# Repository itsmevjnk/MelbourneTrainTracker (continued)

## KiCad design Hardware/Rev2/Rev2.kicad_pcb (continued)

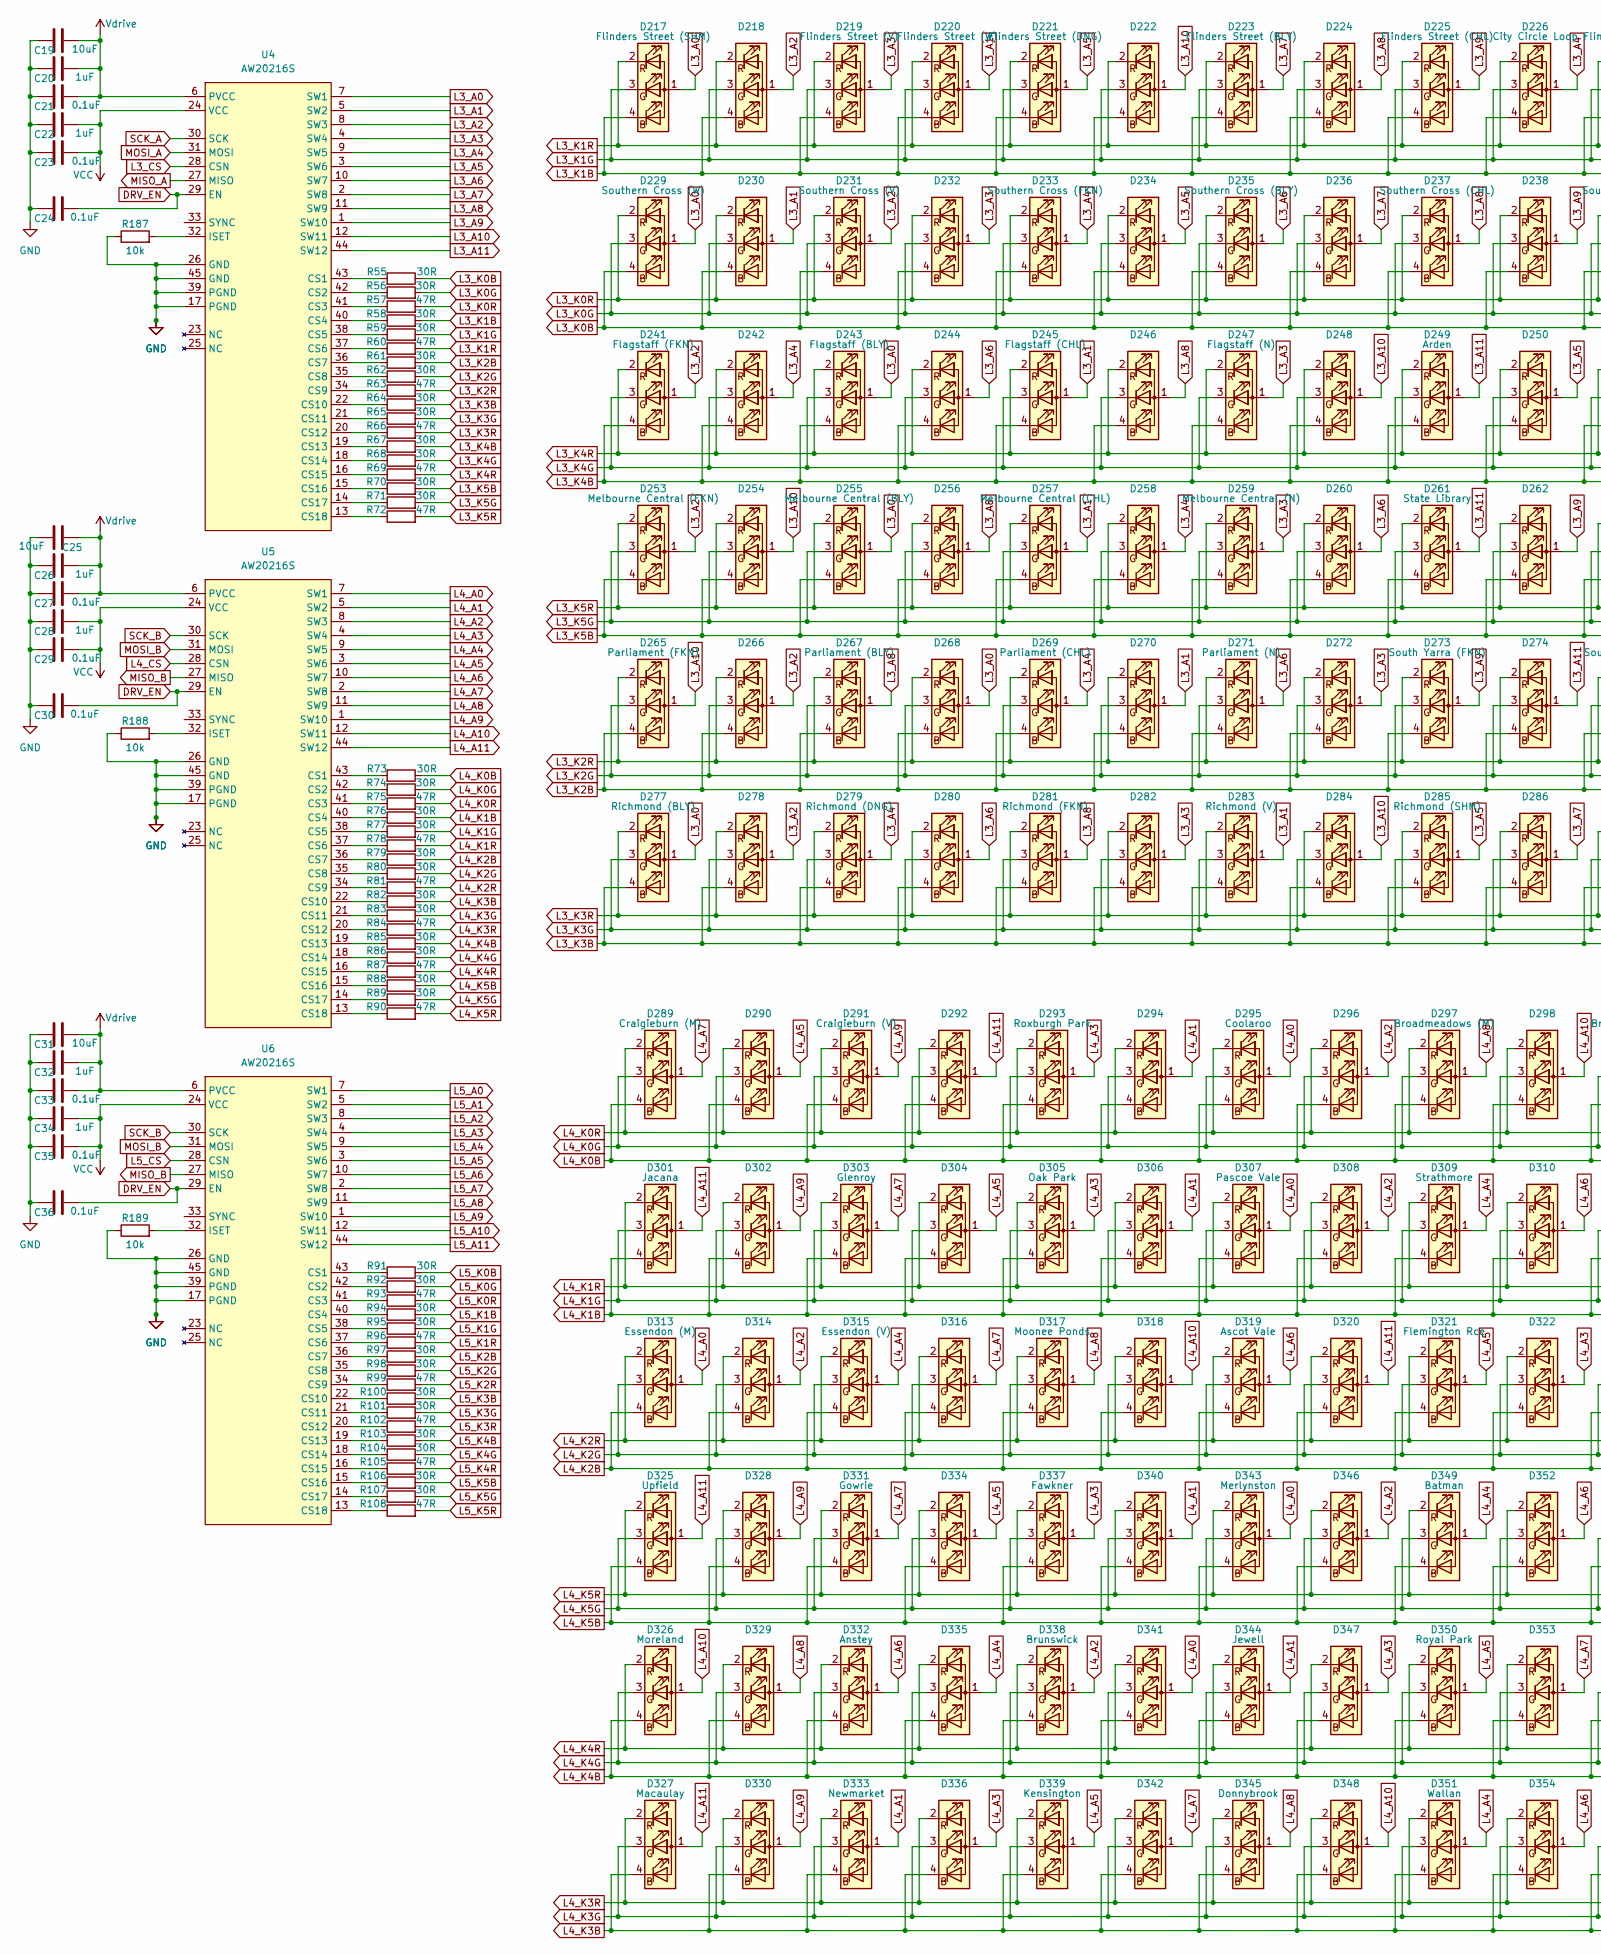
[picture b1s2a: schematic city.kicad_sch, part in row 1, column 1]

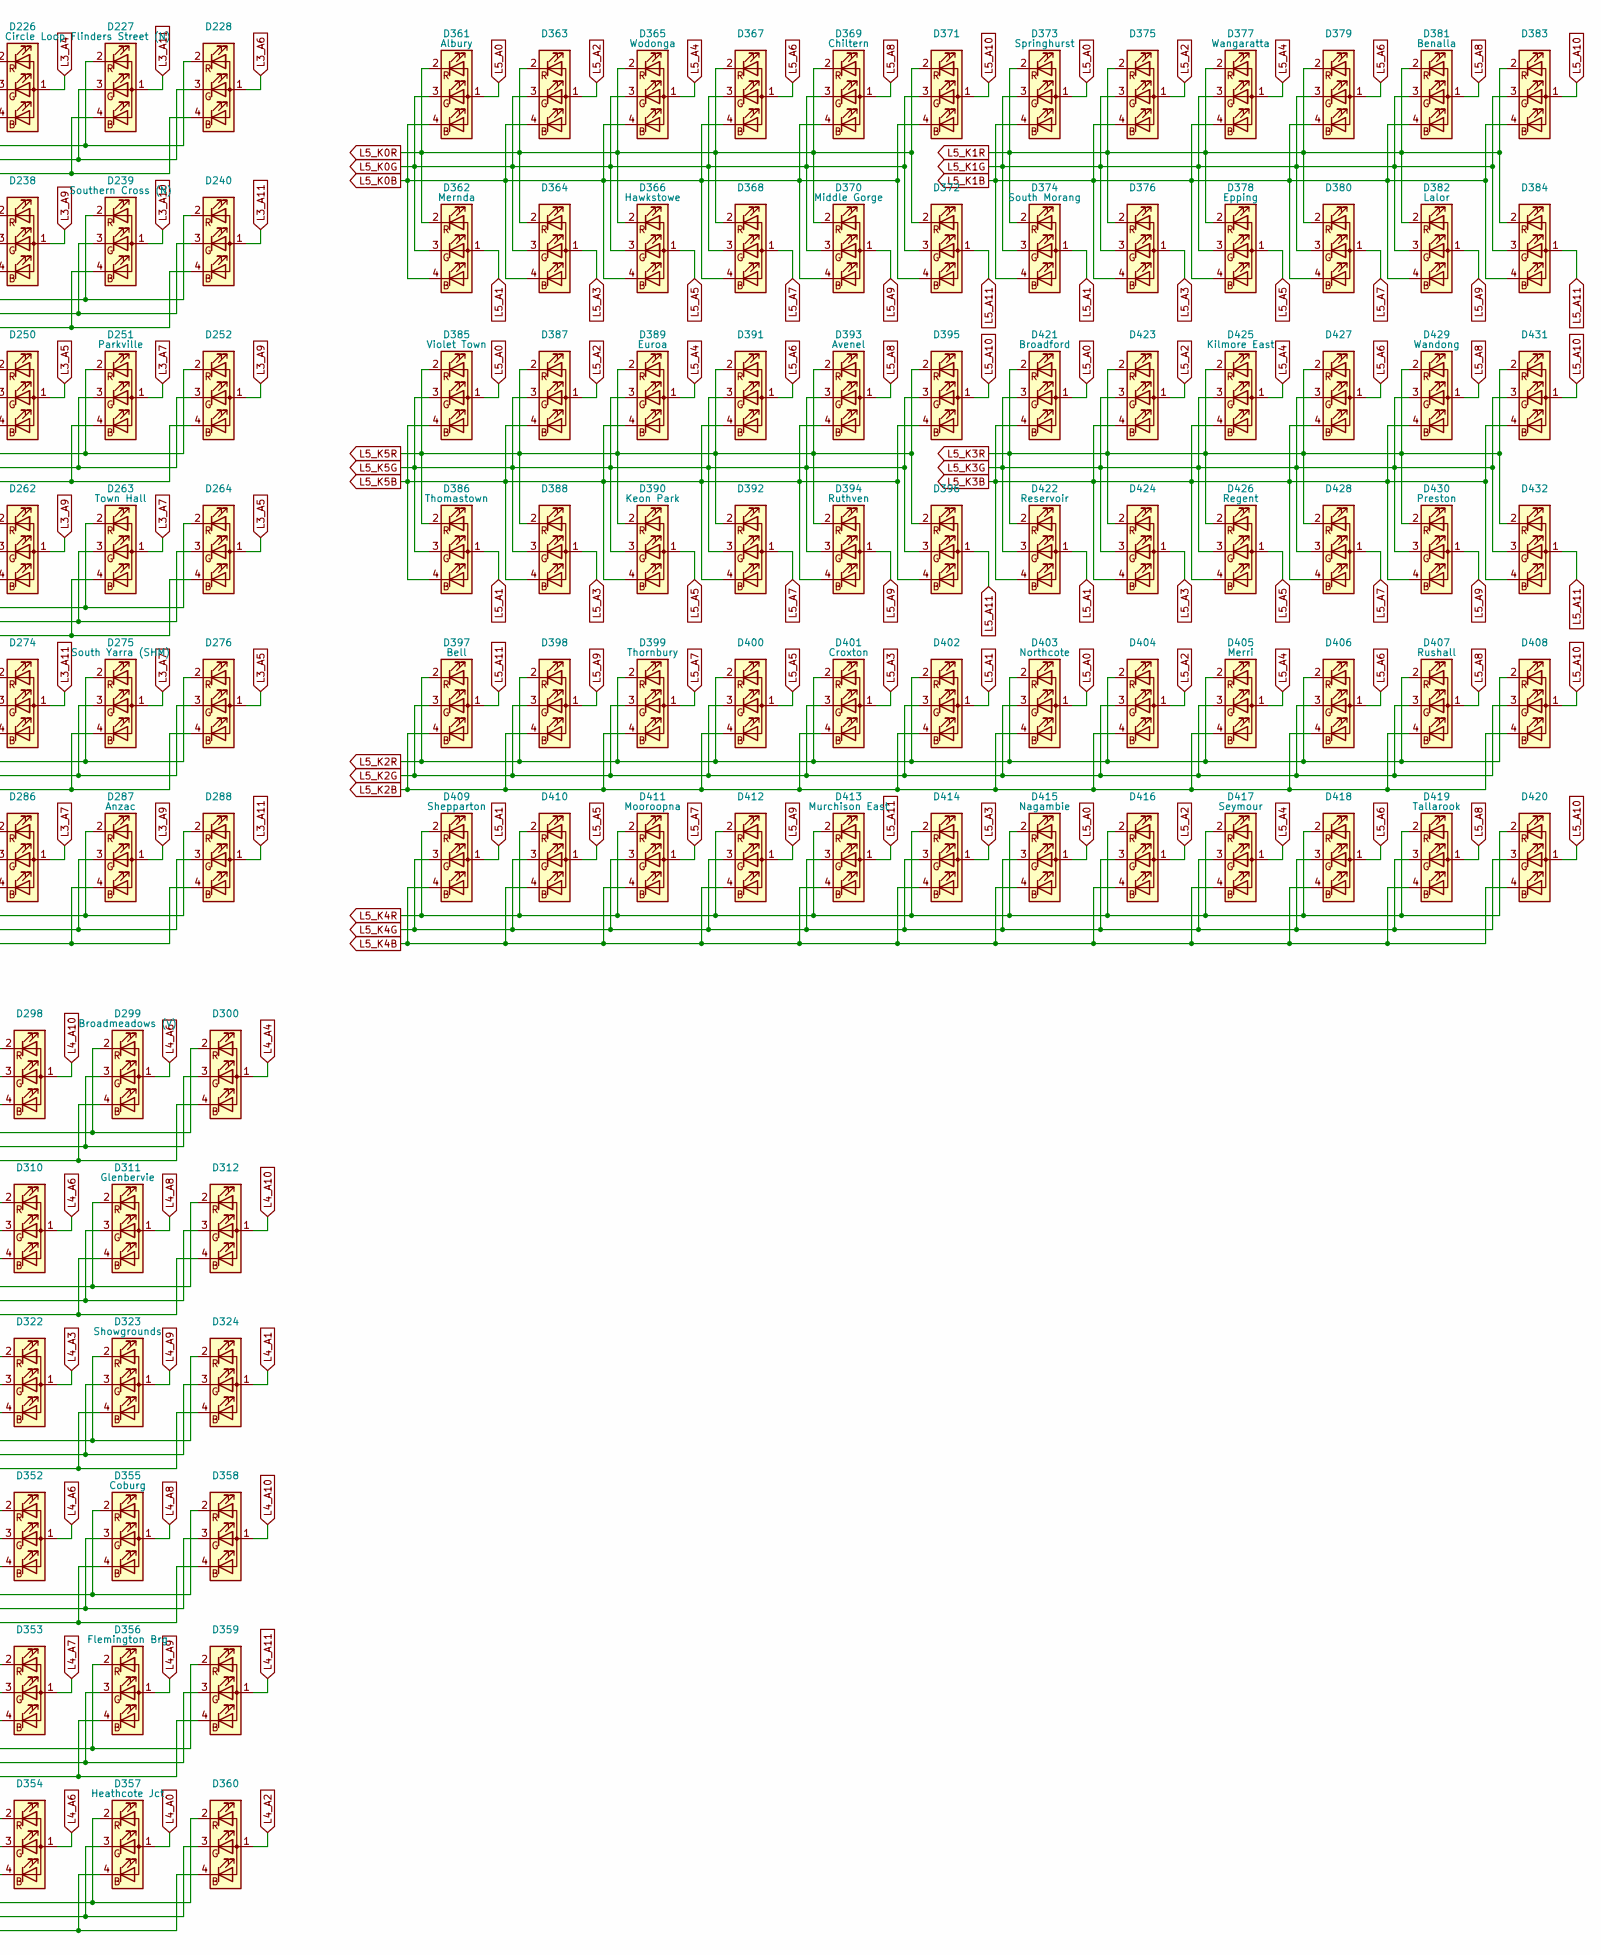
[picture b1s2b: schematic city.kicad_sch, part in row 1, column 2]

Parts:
C19, C25, C31: 10uF; C_0805_2012Metric_Pad1.18x1.45mm_HandSolder; MPN C380332
C20, C22, C26, C28, C32, C34: 1uF; C_0603_1608Metric_Pad1.08x0.95mm_HandSolder; MPN C6119849
C21, C23, C24, C27, C29, C30, C33, C35, C36: 0.1uF; C_0603_1608Metric_Pad1.08x0.95mm_HandSolder; MPN C14663
D217, D218, D219, D220, D221, D222, D223, D224, D225, D226, D227, D228, D229, D230, D231, D232, D233, D234, D235, D236, D237, D238, D239, D240, D241, D242, D243, D244, D245, D246, D247, D248, D249, D250, D251, D252, D253, D254, D255, D256, D257, D258, D259, D260, D261, D262, D263, D264, D265, D266, D267, D268, D269, D270, D271, D272, D273, D274, D275, D276, D277, D278, D279, D280, D281, D282, D283, D284, D285, D286, D287, D288, D289, D290, D291, D292, D293, D294, D295, D296, D297, D298, D299, D300, D301, D302, D303, D304, D305, D306, D307, D308, D309, D310, D311, D312, D313, D314, D315, D316, D317, D318, D319, D320, D321, D322, D323, D324, D325, D326, D327, D328, D329, D330, D331, D332, D333, D334, D335, D336, D337, D338, D339, D340, D341, D342, D343, D344, D345, D346, D347, D348, D349, D350, D351, D352, D353, D354, D355, D356, D357, D358, D359, D360, D361, D362, D363, D364, D365, D366, D367, D368, D369, D370, D371, D372, D373, D374, D375, D376, D377, D378, D379, D380, D381, D382, D383, D384, D385, D386, D387, D388, D389, D390, D391, D392, D393, D394, D395, D396, D397, D398, D399, D400, D401, D402, D403, D404, D405, D406, D407, D408, D409, D410, D411, D412, D413, D414, D415, D416, D417, D418, D419, D420, D421, D422, D423, D424, D425, D426, D427, D428, D429, D430, D431, D432: XL-B1010RGBT-HF; LED_RGB_Xinglight-1010; MPN C22464515
R55, R56, R58, R59, R61, R62, R64, R65, R67, R68, R70, R71, R73, R74, R76, R77, R79, R80, R82, R83, R85, R86, R88, R89, R91, R92, R94, R95, R97, R98, R100, R101, R103, R104, R106, R107: 30R; R_0805_2012Metric_Pad1.20x1.40mm_HandSolder
R57, R60, R63, R66, R69, R72, R75, R78, R81, R84, R87, R90, R93, R96, R99, R102, R105, R108: 47R; R_0805_2012Metric_Pad1.20x1.40mm_HandSolder
R187, R188, R189: 10k; R_0603_1608Metric_Pad0.98x0.95mm_HandSolder; MPN C2930231
U4, U5, U6: AW20216S; QFN-44-1EP_5x5mm_P0.4mm_EP2.45x2.45mm; MPN C7385556

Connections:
+3.3V: C22.2, C23.2, C28.2, C29.2, C34.2, C35.2, U4.24 (VCC), U5.24 (VCC), U6.24 (VCC); also elsewhere on the board
+5V: C19.2, C20.2, C21.2, C25.1, C26.2, C27.2, C31.2, C32.2, C33.2, U4.6 (PVCC), U5.6 (PVCC), U6.6 (PVCC); also elsewhere on the board
DRV_EN: C24.2, C30.2, C36.2, U4.29 (EN), U5.29 (EN), U6.29 (EN); also elsewhere on the board
GND: C19.1, C20.1, C21.1, C22.1, C23.1, C24.1, C25.2, C26.1, C27.1, C28.1, C29.1, C30.1, C31.1, C32.1, C33.1, C34.1, C35.1, C36.1, R187.1, R188.1, R189.1, U4.17 (PGND), U4.26 (GND), U4.39 (PGND), U4.45 (GND), U5.17 (PGND), U5.26 (GND), U5.39 (PGND), U5.45 (GND), U6.17 (PGND), U6.26 (GND), U6.39 (PGND), U6.45 (GND); also elsewhere on the board
L3_A0: D217.1 (A), D229.1 (A), D243.1 (A), D255.1 (A), D268.1 (A), D277.1 (A), U4.7 (SW1)
L3_A1: D220.1 (A), D230.1 (A), D245.1 (A), D257.1 (A), D270.1 (A), D283.1 (A), U4.5 (SW2)
L3_A2: D218.1 (A), D231.1 (A), D241.1 (A), D253.1 (A), D266.1 (A), D278.1 (A), U4.8 (SW3)
L3_A3: D219.1 (A), D232.1 (A), D247.1 (A), D259.1 (A), D272.1 (A), D282.1 (A), U4.4 (SW4)
L3_A4: D226.1 (A), D233.1 (A), D242.1 (A), D258.1 (A), D269.1 (A), D279.1 (A), U4.9 (SW5)
L3_A5: D221.1 (A), D234.1 (A), D250.1 (A), D264.1 (A), D276.1 (A), D285.1 (A), U4.3 (SW6)
L3_A6: D228.1 (A), D235.1 (A), D244.1 (A), D260.1 (A), D271.1 (A), D280.1 (A), U4.10 (SW7)
L3_A7: D223.1 (A), D236.1 (A), D251.1 (A), D263.1 (A), D275.1 (A), D286.1 (A), U4.2 (SW8)
L3_A8: D224.1 (A), D237.1 (A), D246.1 (A), D256.1 (A), D267.1 (A), D281.1 (A), U4.11 (SW9)
L3_A9: D225.1 (A), D238.1 (A), D252.1 (A), D262.1 (A), D273.1 (A), D287.1 (A), U4.1 (SW10)
L3_A10: D222.1 (A), D239.1 (A), D248.1 (A), D254.1 (A), D265.1 (A), D284.1 (A), U4.12 (SW11)
L3_A11: D227.1 (A), D240.1 (A), D249.1 (A), D261.1 (A), D274.1 (A), D288.1 (A), U4.44 (SW12)
L3_CS: U4.28 (CSN); also elsewhere on the board
L3_K0B: D229.4 (BK), D230.4 (BK), D231.4 (BK), D232.4 (BK), D233.4 (BK), D234.4 (BK), D235.4 (BK), D236.4 (BK), D237.4 (BK), D238.4 (BK), D239.4 (BK), D240.4 (BK), R55.1
L3_K0G: D229.3 (GK), D230.3 (GK), D231.3 (GK), D232.3 (GK), D233.3 (GK), D234.3 (GK), D235.3 (GK), D236.3 (GK), D237.3 (GK), D238.3 (GK), D239.3 (GK), D240.3 (GK), R56.2
L3_K0R: D229.2 (RK), D230.2 (RK), D231.2 (RK), D232.2 (RK), D233.2 (RK), D234.2 (RK), D235.2 (RK), D236.2 (RK), D237.2 (RK), D238.2 (RK), D239.2 (RK), D240.2 (RK), R57.2
L3_K1B: D217.4 (BK), D218.4 (BK), D219.4 (BK), D220.4 (BK), D221.4 (BK), D222.4 (BK), D223.4 (BK), D224.4 (BK), D225.4 (BK), D226.4 (BK), D227.4 (BK), D228.4 (BK), R58.2
L3_K1G: D217.3 (GK), D218.3 (GK), D219.3 (GK), D220.3 (GK), D221.3 (GK), D222.3 (GK), D223.3 (GK), D224.3 (GK), D225.3 (GK), D226.3 (GK), D227.3 (GK), D228.3 (GK), R59.2
L3_K1R: D217.2 (RK), D218.2 (RK), D219.2 (RK), D220.2 (RK), D221.2 (RK), D222.2 (RK), D223.2 (RK), D224.2 (RK), D225.2 (RK), D226.2 (RK), D227.2 (RK), D228.2 (RK), R60.2
L3_K2B: D265.4 (BK), D266.4 (BK), D267.4 (BK), D268.4 (BK), D269.4 (BK), D270.4 (BK), D271.4 (BK), D272.4 (BK), D273.4 (BK), D274.4 (BK), D275.4 (BK), D276.4 (BK), R61.2
L3_K2G: D265.3 (GK), D266.3 (GK), D267.3 (GK), D268.3 (GK), D269.3 (GK), D270.3 (GK), D271.3 (GK), D272.3 (GK), D273.3 (GK), D274.3 (GK), D275.3 (GK), D276.3 (GK), R62.2
L3_K2R: D265.2 (RK), D266.2 (RK), D267.2 (RK), D268.2 (RK), D269.2 (RK), D270.2 (RK), D271.2 (RK), D272.2 (RK), D273.2 (RK), D274.2 (RK), D275.2 (RK), D276.2 (RK), R63.2
L3_K3B: D277.4 (BK), D278.4 (BK), D279.4 (BK), D280.4 (BK), D281.4 (BK), D282.4 (BK), D283.4 (BK), D284.4 (BK), D285.4 (BK), D286.4 (BK), D287.4 (BK), D288.4 (BK), R64.2
L3_K3G: D277.3 (GK), D278.3 (GK), D279.3 (GK), D280.3 (GK), D281.3 (GK), D282.3 (GK), D283.3 (GK), D284.3 (GK), D285.3 (GK), D286.3 (GK), D287.3 (GK), D288.3 (GK), R65.2
L3_K3R: D277.2 (RK), D278.2 (RK), D279.2 (RK), D280.2 (RK), D281.2 (RK), D282.2 (RK), D283.2 (RK), D284.2 (RK), D285.2 (RK), D286.2 (RK), D287.2 (RK), D288.2 (RK), R66.2
L3_K4B: D241.4 (BK), D242.4 (BK), D243.4 (BK), D244.4 (BK), D245.4 (BK), D246.4 (BK), D247.4 (BK), D248.4 (BK), D249.4 (BK), D250.4 (BK), D251.4 (BK), D252.4 (BK), R67.2
L3_K4G: D241.3 (GK), D242.3 (GK), D243.3 (GK), D244.3 (GK), D245.3 (GK), D246.3 (GK), D247.3 (GK), D248.3 (GK), D249.3 (GK), D250.3 (GK), D251.3 (GK), D252.3 (GK), R68.2
L3_K4R: D241.2 (RK), D242.2 (RK), D243.2 (RK), D244.2 (RK), D245.2 (RK), D246.2 (RK), D247.2 (RK), D248.2 (RK), D249.2 (RK), D250.2 (RK), D251.2 (RK), D252.2 (RK), R69.2
L3_K5B: D253.4 (BK), D254.4 (BK), D255.4 (BK), D256.4 (BK), D257.4 (BK), D258.4 (BK), D259.4 (BK), D260.4 (BK), D261.4 (BK), D262.4 (BK), D263.4 (BK), D264.4 (BK), R70.2
L3_K5G: D253.3 (GK), D254.3 (GK), D255.3 (GK), D256.3 (GK), D257.3 (GK), D258.3 (GK), D259.3 (GK), D260.3 (GK), D261.3 (GK), D262.3 (GK), D263.3 (GK), D264.3 (GK), R71.2
L3_K5R: D253.2 (RK), D254.2 (RK), D255.2 (RK), D256.2 (RK), D257.2 (RK), D258.2 (RK), D259.2 (RK), D260.2 (RK), D261.2 (RK), D262.2 (RK), D263.2 (RK), D264.2 (RK), R72.2
L4_A0: D295.1 (A), D307.1 (A), D313.1 (A), D341.1 (A), D343.1 (A), D357.1 (A), U5.7 (SW1)
L4_A1: D294.1 (A), D306.1 (A), D324.1 (A), D333.1 (A), D340.1 (A), D344.1 (A), U5.5 (SW2)
L4_A2: D296.1 (A), D308.1 (A), D314.1 (A), D338.1 (A), D346.1 (A), D360.1 (A), U5.8 (SW3)
L4_A3: D293.1 (A), D305.1 (A), D322.1 (A), D336.1 (A), D337.1 (A), D347.1 (A), U5.4 (SW4)
L4_A4: D300.1 (A), D309.1 (A), D315.1 (A), D335.1 (A), D349.1 (A), D351.1 (A), U5.9 (SW5)
L4_A5: D290.1 (A), D304.1 (A), D321.1 (A), D334.1 (A), D339.1 (A), D350.1 (A), U5.3 (SW6)
L4_A6: D299.1 (A), D310.1 (A), D319.1 (A), D332.1 (A), D352.1 (A), D354.1 (A), U5.10 (SW7)
L4_A7: D289.1 (A), D303.1 (A), D316.1 (A), D331.1 (A), D342.1 (A), D353.1 (A), U5.2 (SW8)
L4_A8: D297.1 (A), D311.1 (A), D317.1 (A), D329.1 (A), D345.1 (A), D355.1 (A), U5.11 (SW9)
L4_A9: D291.1 (A), D302.1 (A), D323.1 (A), D328.1 (A), D330.1 (A), D356.1 (A), U5.1 (SW10)
L4_A10: D298.1 (A), D312.1 (A), D318.1 (A), D326.1 (A), D348.1 (A), D358.1 (A), U5.12 (SW11)
L4_A11: D292.1 (A), D301.1 (A), D320.1 (A), D325.1 (A), D327.1 (A), D359.1 (A), U5.44 (SW12)
L4_CS: U5.28 (CSN); also elsewhere on the board
L4_K0B: D289.4 (BK), D290.4 (BK), D291.4 (BK), D292.4 (BK), D293.4 (BK), D294.4 (BK), D295.4 (BK), D296.4 (BK), D297.4 (BK), D298.4 (BK), D299.4 (BK), D300.4 (BK), R73.1
L4_K0G: D289.3 (GK), D290.3 (GK), D291.3 (GK), D292.3 (GK), D293.3 (GK), D294.3 (GK), D295.3 (GK), D296.3 (GK), D297.3 (GK), D298.3 (GK), D299.3 (GK), D300.3 (GK), R74.2
L4_K0R: D289.2 (RK), D290.2 (RK), D291.2 (RK), D292.2 (RK), D293.2 (RK), D294.2 (RK), D295.2 (RK), D296.2 (RK), D297.2 (RK), D298.2 (RK), D299.2 (RK), D300.2 (RK), R75.2
L4_K1B: D301.4 (BK), D302.4 (BK), D303.4 (BK), D304.4 (BK), D305.4 (BK), D306.4 (BK), D307.4 (BK), D308.4 (BK), D309.4 (BK), D310.4 (BK), D311.4 (BK), D312.4 (BK), R76.2
L4_K1G: D301.3 (GK), D302.3 (GK), D303.3 (GK), D304.3 (GK), D305.3 (GK), D306.3 (GK), D307.3 (GK), D308.3 (GK), D309.3 (GK), D310.3 (GK), D311.3 (GK), D312.3 (GK), R77.2
L4_K1R: D301.2 (RK), D302.2 (RK), D303.2 (RK), D304.2 (RK), D305.2 (RK), D306.2 (RK), D307.2 (RK), D308.2 (RK), D309.2 (RK), D310.2 (RK), D311.2 (RK), D312.2 (RK), R78.2
L4_K2B: D313.4 (BK), D314.4 (BK), D315.4 (BK), D316.4 (BK), D317.4 (BK), D318.4 (BK), D319.4 (BK), D320.4 (BK), D321.4 (BK), D322.4 (BK), D323.4 (BK), D324.4 (BK), R79.2
L4_K2G: D313.3 (GK), D314.3 (GK), D315.3 (GK), D316.3 (GK), D317.3 (GK), D318.3 (GK), D319.3 (GK), D320.3 (GK), D321.3 (GK), D322.3 (GK), D323.3 (GK), D324.3 (GK), R80.2
L4_K2R: D313.2 (RK), D314.2 (RK), D315.2 (RK), D316.2 (RK), D317.2 (RK), D318.2 (RK), D319.2 (RK), D320.2 (RK), D321.2 (RK), D322.2 (RK), D323.2 (RK), D324.2 (RK), R81.2
L4_K3B: D327.4 (BK), D330.4 (BK), D333.4 (BK), D336.4 (BK), D339.4 (BK), D342.4 (BK), D345.4 (BK), D348.4 (BK), D351.4 (BK), D354.4 (BK), D357.4 (BK), D360.4 (BK), R82.2
L4_K3G: D327.3 (GK), D330.3 (GK), D333.3 (GK), D336.3 (GK), D339.3 (GK), D342.3 (GK), D345.3 (GK), D348.3 (GK), D351.3 (GK), D354.3 (GK), D357.3 (GK), D360.3 (GK), R83.2
L4_K3R: D327.2 (RK), D330.2 (RK), D333.2 (RK), D336.2 (RK), D339.2 (RK), D342.2 (RK), D345.2 (RK), D348.2 (RK), D351.2 (RK), D354.2 (RK), D357.2 (RK), D360.2 (RK), R84.2
L4_K4B: D326.4 (BK), D329.4 (BK), D332.4 (BK), D335.4 (BK), D338.4 (BK), D341.4 (BK), D344.4 (BK), D347.4 (BK), D350.4 (BK), D353.4 (BK), D356.4 (BK), D359.4 (BK), R85.2
L4_K4G: D326.3 (GK), D329.3 (GK), D332.3 (GK), D335.3 (GK), D338.3 (GK), D341.3 (GK), D344.3 (GK), D347.3 (GK), D350.3 (GK), D353.3 (GK), D356.3 (GK), D359.3 (GK), R86.2
L4_K4R: D326.2 (RK), D329.2 (RK), D332.2 (RK), D335.2 (RK), D338.2 (RK), D341.2 (RK), D344.2 (RK), D347.2 (RK), D350.2 (RK), D353.2 (RK), D356.2 (RK), D359.2 (RK), R87.2
L4_K5B: D325.4 (BK), D328.4 (BK), D331.4 (BK), D334.4 (BK), D337.4 (BK), D340.4 (BK), D343.4 (BK), D346.4 (BK), D349.4 (BK), D352.4 (BK), D355.4 (BK), D358.4 (BK), R88.2
L4_K5G: D325.3 (GK), D328.3 (GK), D331.3 (GK), D334.3 (GK), D337.3 (GK), D340.3 (GK), D343.3 (GK), D346.3 (GK), D349.3 (GK), D352.3 (GK), D355.3 (GK), D358.3 (GK), R89.2
L4_K5R: D325.2 (RK), D328.2 (RK), D331.2 (RK), D334.2 (RK), D337.2 (RK), D340.2 (RK), D343.2 (RK), D346.2 (RK), D349.2 (RK), D352.2 (RK), D355.2 (RK), D358.2 (RK), R90.2
L5_A0: D361.1 (A), D373.1 (A), D385.1 (A), D403.1 (A), D415.1 (A), D421.1 (A), U6.7 (SW1)
L5_A1: D362.1 (A), D374.1 (A), D386.1 (A), D402.1 (A), D409.1 (A), D422.1 (A), U6.5 (SW2)
L5_A2: D363.1 (A), D375.1 (A), D387.1 (A), D404.1 (A), D416.1 (A), D423.1 (A), U6.8 (SW3)
L5_A3: D364.1 (A), D376.1 (A), D388.1 (A), D401.1 (A), D414.1 (A), D424.1 (A), U6.4 (SW4)
L5_A4: D365.1 (A), D377.1 (A), D389.1 (A), D405.1 (A), D417.1 (A), D425.1 (A), U6.9 (SW5)
L5_A5: D366.1 (A), D378.1 (A), D390.1 (A), D400.1 (A), D410.1 (A), D426.1 (A), U6.3 (SW6)
L5_A6: D367.1 (A), D379.1 (A), D391.1 (A), D406.1 (A), D418.1 (A), D427.1 (A), U6.10 (SW7)
L5_A7: D368.1 (A), D380.1 (A), D392.1 (A), D399.1 (A), D411.1 (A), D428.1 (A), U6.2 (SW8)
L5_A8: D369.1 (A), D381.1 (A), D393.1 (A), D407.1 (A), D419.1 (A), D429.1 (A), U6.11 (SW9)
L5_A9: D370.1 (A), D382.1 (A), D394.1 (A), D398.1 (A), D412.1 (A), D430.1 (A), U6.1 (SW10)
L5_A10: D371.1 (A), D383.1 (A), D395.1 (A), D408.1 (A), D420.1 (A), D431.1 (A), U6.12 (SW11)
L5_A11: D372.1 (A), D384.1 (A), D396.1 (A), D397.1 (A), D413.1 (A), D432.1 (A), U6.44 (SW12)
L5_CS: U6.28 (CSN); also elsewhere on the board
L5_K0B: D361.4 (BK), D362.4 (BK), D363.4 (BK), D364.4 (BK), D365.4 (BK), D366.4 (BK), D367.4 (BK), D368.4 (BK), D369.4 (BK), D370.4 (BK), D371.4 (BK), D372.4 (BK), R91.1
L5_K0G: D361.3 (GK), D362.3 (GK), D363.3 (GK), D364.3 (GK), D365.3 (GK), D366.3 (GK), D367.3 (GK), D368.3 (GK), D369.3 (GK), D370.3 (GK), D371.3 (GK), D372.3 (GK), R92.2
L5_K0R: D361.2 (RK), D362.2 (RK), D363.2 (RK), D364.2 (RK), D365.2 (RK), D366.2 (RK), D367.2 (RK), D368.2 (RK), D369.2 (RK), D370.2 (RK), D371.2 (RK), D372.2 (RK), R93.2
L5_K1B: D373.4 (BK), D374.4 (BK), D375.4 (BK), D376.4 (BK), D377.4 (BK), D378.4 (BK), D379.4 (BK), D380.4 (BK), D381.4 (BK), D382.4 (BK), D383.4 (BK), D384.4 (BK), R94.2
L5_K1G: D373.3 (GK), D374.3 (GK), D375.3 (GK), D376.3 (GK), D377.3 (GK), D378.3 (GK), D379.3 (GK), D380.3 (GK), D381.3 (GK), D382.3 (GK), D383.3 (GK), D384.3 (GK), R95.2
L5_K1R: D373.2 (RK), D374.2 (RK), D375.2 (RK), D376.2 (RK), D377.2 (RK), D378.2 (RK), D379.2 (RK), D380.2 (RK), D381.2 (RK), D382.2 (RK), D383.2 (RK), D384.2 (RK), R96.2
L5_K2B: D397.4 (BK), D398.4 (BK), D399.4 (BK), D400.4 (BK), D401.4 (BK), D402.4 (BK), D403.4 (BK), D404.4 (BK), D405.4 (BK), D406.4 (BK), D407.4 (BK), D408.4 (BK), R97.2
L5_K2G: D397.3 (GK), D398.3 (GK), D399.3 (GK), D400.3 (GK), D401.3 (GK), D402.3 (GK), D403.3 (GK), D404.3 (GK), D405.3 (GK), D406.3 (GK), D407.3 (GK), D408.3 (GK), R98.2
L5_K2R: D397.2 (RK), D398.2 (RK), D399.2 (RK), D400.2 (RK), D401.2 (RK), D402.2 (RK), D403.2 (RK), D404.2 (RK), D405.2 (RK), D406.2 (RK), D407.2 (RK), D408.2 (RK), R99.2
L5_K3B: D421.4 (BK), D422.4 (BK), D423.4 (BK), D424.4 (BK), D425.4 (BK), D426.4 (BK), D427.4 (BK), D428.4 (BK), D429.4 (BK), D430.4 (BK), D431.4 (BK), D432.4 (BK), R100.2
L5_K3G: D421.3 (GK), D422.3 (GK), D423.3 (GK), D424.3 (GK), D425.3 (GK), D426.3 (GK), D427.3 (GK), D428.3 (GK), D429.3 (GK), D430.3 (GK), D431.3 (GK), D432.3 (GK), R101.2
L5_K3R: D421.2 (RK), D422.2 (RK), D423.2 (RK), D424.2 (RK), D425.2 (RK), D426.2 (RK), D427.2 (RK), D428.2 (RK), D429.2 (RK), D430.2 (RK), D431.2 (RK), D432.2 (RK), R102.2
L5_K4B: D409.4 (BK), D410.4 (BK), D411.4 (BK), D412.4 (BK), D413.4 (BK), D414.4 (BK), D415.4 (BK), D416.4 (BK), D417.4 (BK), D418.4 (BK), D419.4 (BK), D420.4 (BK), R103.2
L5_K4G: D409.3 (GK), D410.3 (GK), D411.3 (GK), D412.3 (GK), D413.3 (GK), D414.3 (GK), D415.3 (GK), D416.3 (GK), D417.3 (GK), D418.3 (GK), D419.3 (GK), D420.3 (GK), R104.2
L5_K4R: D409.2 (RK), D410.2 (RK), D411.2 (RK), D412.2 (RK), D413.2 (RK), D414.2 (RK), D415.2 (RK), D416.2 (RK), D417.2 (RK), D418.2 (RK), D419.2 (RK), D420.2 (RK), R105.2
L5_K5B: D385.4 (BK), D386.4 (BK), D387.4 (BK), D388.4 (BK), D389.4 (BK), D390.4 (BK), D391.4 (BK), D392.4 (BK), D393.4 (BK), D394.4 (BK), D395.4 (BK), D396.4 (BK), R106.2
L5_K5G: D385.3 (GK), D386.3 (GK), D387.3 (GK), D388.3 (GK), D389.3 (GK), D390.3 (GK), D391.3 (GK), D392.3 (GK), D393.3 (GK), D394.3 (GK), D395.3 (GK), D396.3 (GK), R107.2
L5_K5R: D385.2 (RK), D386.2 (RK), D387.2 (RK), D388.2 (RK), D389.2 (RK), D390.2 (RK), D391.2 (RK), D392.2 (RK), D393.2 (RK), D394.2 (RK), D395.2 (RK), D396.2 (RK), R108.2
MISO_A: U4.27 (MISO); also elsewhere on the board
MISO_B: U5.27 (MISO), U6.27 (MISO); also elsewhere on the board
MOSI_A: U4.31 (MOSI); also elsewhere on the board
MOSI_B: U5.31 (MOSI), U6.31 (MOSI); also elsewhere on the board
unnamed: R55.2, U4.43 (CS1)
unnamed: R56.1, U4.42 (CS2)
unnamed: R57.1, U4.41 (CS3)
unnamed: R58.1, U4.40 (CS4)
unnamed: R59.1, U4.38 (CS5)
unnamed: R60.1, U4.37 (CS6)
unnamed: R61.1, U4.36 (CS7)
unnamed: R62.1, U4.35 (CS8)
unnamed: R63.1, U4.34 (CS9)
unnamed: R64.1, U4.22 (CS10)
unnamed: R65.1, U4.21 (CS11)
unnamed: R66.1, U4.20 (CS12)
unnamed: R67.1, U4.19 (CS13)
unnamed: R68.1, U4.18 (CS14)
unnamed: R69.1, U4.16 (CS15)
unnamed: R70.1, U4.15 (CS16)
unnamed: R71.1, U4.14 (CS17)
unnamed: R72.1, U4.13 (CS18)
unnamed: R187.2, U4.32 (ISET)
unnamed: R73.2, U5.43 (CS1)
unnamed: R74.1, U5.42 (CS2)
unnamed: R75.1, U5.41 (CS3)
unnamed: R76.1, U5.40 (CS4)
unnamed: R77.1, U5.38 (CS5)
unnamed: R78.1, U5.37 (CS6)
unnamed: R79.1, U5.36 (CS7)
unnamed: R80.1, U5.35 (CS8)
unnamed: R81.1, U5.34 (CS9)
unnamed: R82.1, U5.22 (CS10)
unnamed: R83.1, U5.21 (CS11)
unnamed: R84.1, U5.20 (CS12)
unnamed: R85.1, U5.19 (CS13)
unnamed: R86.1, U5.18 (CS14)
unnamed: R87.1, U5.16 (CS15)
unnamed: R88.1, U5.15 (CS16)
unnamed: R89.1, U5.14 (CS17)
unnamed: R90.1, U5.13 (CS18)
unnamed: R188.2, U5.32 (ISET)
unnamed: R91.2, U6.43 (CS1)
unnamed: R92.1, U6.42 (CS2)
unnamed: R93.1, U6.41 (CS3)
unnamed: R94.1, U6.40 (CS4)
unnamed: R95.1, U6.38 (CS5)
unnamed: R96.1, U6.37 (CS6)
unnamed: R97.1, U6.36 (CS7)
unnamed: R98.1, U6.35 (CS8)
unnamed: R99.1, U6.34 (CS9)
unnamed: R100.1, U6.22 (CS10)
unnamed: R101.1, U6.21 (CS11)
unnamed: R102.1, U6.20 (CS12)
unnamed: R103.1, U6.19 (CS13)
unnamed: R104.1, U6.18 (CS14)
unnamed: R105.1, U6.16 (CS15)
unnamed: R106.1, U6.15 (CS16)
unnamed: R107.1, U6.14 (CS17)
unnamed: R108.1, U6.13 (CS18)
unnamed: R189.2, U6.32 (ISET)
SCK_A: U4.30 (SCK); also elsewhere on the board
SCK_B: U5.30 (SCK), U6.30 (SCK); also elsewhere on the board

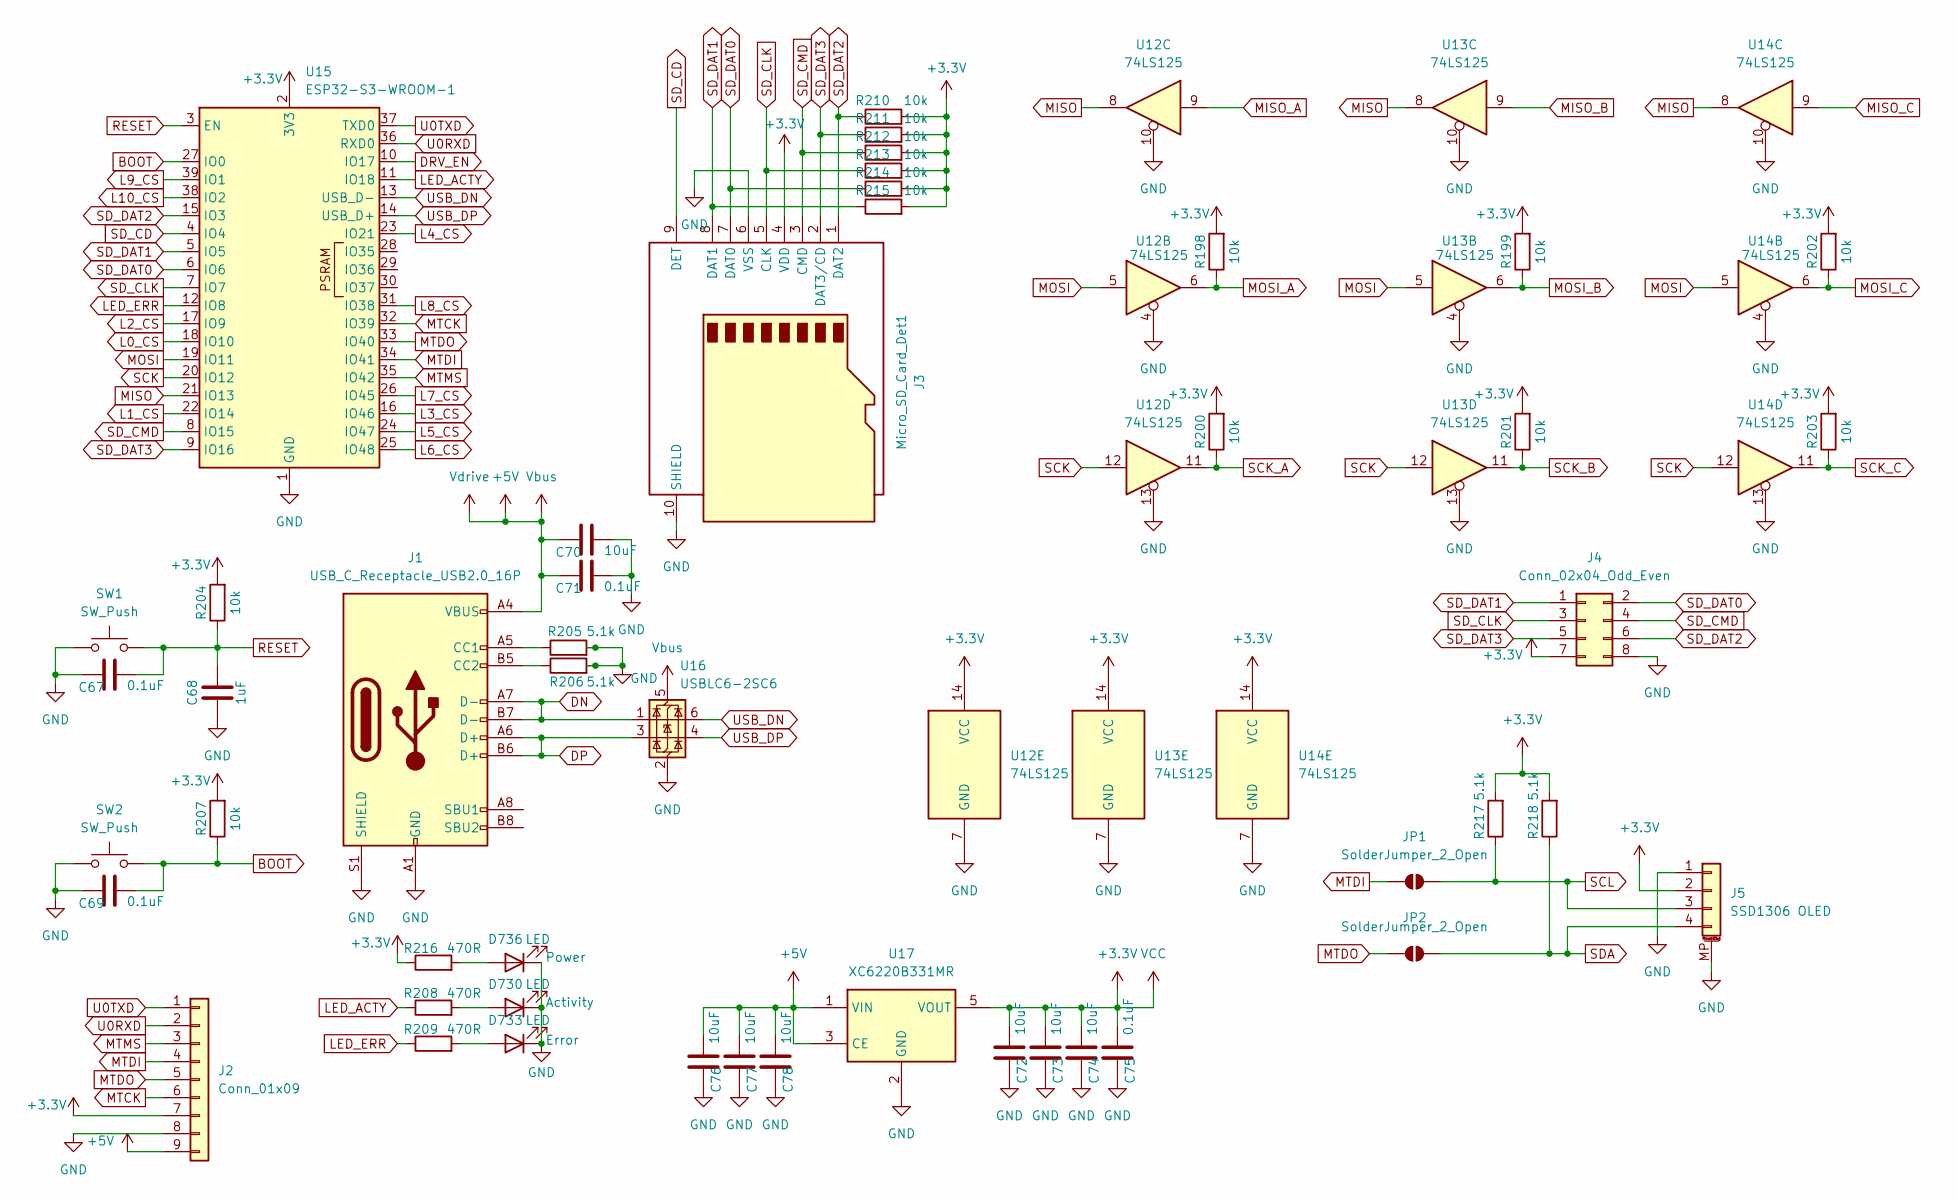
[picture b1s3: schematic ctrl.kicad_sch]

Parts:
C67, C69, C71, C75: 0.1uF; C_0603_1608Metric_Pad1.08x0.95mm_HandSolder; MPN C14663
C68: 1uF; C_0603_1608Metric_Pad1.08x0.95mm_HandSolder; MPN C6119849
C70, C72, C73, C74, C76, C77, C78: 10uF; C_0805_2012Metric_Pad1.18x1.45mm_HandSolder; MPN C380332
D730, D733, D736: LED; LED_1206_3216Metric_Pad1.42x1.75mm_HandSolder; MPN C965822
J1: USB_C_Receptacle_USB2.0_16P; ShouHan-USBC-16P-2MD; MPN C2765186
J2: Conn_01x09; PinHeader_1x09_P2.54mm_Vertical; MPN C49451372
J3: Micro_SD_Card_Det1; TFW11-N1S1-2000-A; MPN C22357898
J4: Conn_02x04_Odd_Even; PinHeader_2x04_P2.54mm_Vertical
J5: SSD1306 OLED; HS96L03W2C03
JP1, JP2: SolderJumper_2_Open; SolderJumper-2_P1.3mm_Open_TrianglePad1.0x1.5mm
R198, R199, R200, R201, R202, R203, R204, R207, R210, R211, R212, R213, R214, R215: 10k; R_0603_1608Metric_Pad0.98x0.95mm_HandSolder; MPN C15401
R205, R206, R217, R218: 5.1k; R_0603_1608Metric_Pad0.98x0.95mm_HandSolder; MPN C328370
R208, R209: 470R; R_0603_1608Metric_Pad0.98x0.95mm_HandSolder; MPN C23179
R216: 470R; R_0603_1608Metric_Pad0.98x0.95mm_HandSolder; MPN C2907127
SW1, SW2: SW_Push; SW_Push_1P1T_NO_E-Switch_TL3301NxxxxxG; MPN C5342967
U12, U13, U14: 74LS125; SO-14_3.9x8.65mm_P1.27mm; MPN C5138994
U15: ESP32-S3-WROOM-1; MPN C2913201
U16: USBLC6-2SC6; SOT-23-6
U17: XC6220B331MR; SOT-23-5

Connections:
+3.3V: C72.2, C73.2, C74.2, C75.2, J2.7, J3.4 (VDD), J4.7, J5.2, R198.2, R199.2, R200.2, R201.2, R202.2, R203.2, R204.2, R207.2, R210.2, R211.2, R212.2, R213.2, R214.2, R215.2, R216.1, R217.2, R218.2, U12.14 (VCC), U13.14 (VCC), U14.14 (VCC), U15.2 (3V3), U17.5 (VOUT); also elsewhere on the board
+5V: C70.1, C71.1, C76.2, C77.2, C78.2, J1.A4 (VBUS), J1.A9 (VBUS), J1.B4 (VBUS), J1.B9 (VBUS), J2.9, U16.5 (VBUS), U17.1 (VIN), U17.3 (CE); also elsewhere on the board
BOOT: C69.2, R207.1, SW2.2, U15.27 (IO0)
DN: J1.A7 (D-), J1.B7 (D-), U16.1 (I/O1)
DP: J1.A6 (D+), J1.B6 (D+), U16.3 (I/O2)
DRV_EN: U15.10 (IO17); also elsewhere on the board
GND: C67.1, C68.1, C69.1, C70.2, C71.2, C72.1, C73.1, C74.1, C75.1, C76.1, C77.1, C78.1, D730.1 (K), D733.1 (K), D736.1 (K), J1.A1 (GND), J1.A12 (GND), J1.B1 (GND), J1.B12 (GND), J1.S1 (SHIELD), J2.8, J3.6 (VSS), J3.10 (SHIELD), J4.8, J5.1, J5.MP (MountPin), R205.2, R206.2, SW1.1, SW2.1, U12.4, U12.7 (GND), U12.10, U12.13, U13.4, U13.7 (GND), U13.10, U13.13, U14.4, U14.7 (GND), U14.10, U14.13, U15.1 (GND), U15.40 (GND), U15.41 (GND), U16.2 (GND), U17.2 (GND); also elsewhere on the board
L0_CS: U15.18 (IO10); also elsewhere on the board
L1_CS: U15.22 (IO14); also elsewhere on the board
L2_CS: U15.17 (IO9); also elsewhere on the board
L3_CS: U15.16 (IO46); also elsewhere on the board
L4_CS: U15.23 (IO21); also elsewhere on the board
L5_CS: U15.24 (IO47); also elsewhere on the board
L6_CS: U15.25 (IO48); also elsewhere on the board
L7_CS: U15.26 (IO45); also elsewhere on the board
L8_CS: U15.31 (IO38); also elsewhere on the board
L9_CS: U15.39 (IO1); also elsewhere on the board
L10_CS: U15.38 (IO2); also elsewhere on the board
LED_ACTY: R208.1, U15.11 (IO18)
LED_ERR: R209.1, U15.12 (IO8)
MISO: U12.8, U13.8, U14.8, U15.21 (IO13)
MISO_A: U12.9; also elsewhere on the board
MISO_B: U13.9; also elsewhere on the board
MISO_C: U14.9; also elsewhere on the board
MOSI: U12.5, U13.5, U14.5, U15.19 (IO11)
MOSI_A: R198.1, U12.6; also elsewhere on the board
MOSI_B: R199.1, U13.6; also elsewhere on the board
MOSI_C: R202.1, U14.6; also elsewhere on the board
MTCK: J2.6, U15.32 (IO39)
MTDI: J2.4, JP1.1 (A), U15.34 (IO41)
MTDO: J2.5, JP2.1 (A), U15.33 (IO40)
MTMS: J2.3, U15.35 (IO42)
unnamed: D730.2 (A), R208.2
unnamed: D733.2 (A), R209.2
unnamed: D736.2 (A), R216.2
unnamed: J1.A5 (CC1), R205.1
unnamed: J1.B5 (CC2), R206.1
RESET: C67.2, C68.2, R204.1, SW1.2, U15.3 (EN)
SCK: U12.12, U13.12, U14.12, U15.20 (IO12)
SCK_A: R200.1, U12.11; also elsewhere on the board
SCK_B: R201.1, U13.11; also elsewhere on the board
SCK_C: R203.1, U14.11; also elsewhere on the board
SCL: J5.3, JP1.2 (B), R217.1
SDA: J5.4, JP2.2 (B), R218.1
SD_CD: J3.9 (DET), U15.4 (IO4)
SD_CLK: J3.5 (CLK), J4.3, R213.1, U15.7 (IO7)
SD_CMD: J3.3 (CMD), J4.4, R212.1, U15.8 (IO15)
SD_DAT0: J3.7 (DAT0), J4.2, R214.1, U15.6 (IO6)
SD_DAT1: J3.8 (DAT1), J4.1, R215.1, U15.5 (IO5)
SD_DAT2: J3.1 (DAT2), J4.6, R210.1, U15.15 (IO3)
SD_DAT3: J3.2 (DAT3/CD), J4.5, R211.1, U15.9 (IO16)
U0RXD: J2.2, U15.36 (RXD0)
U0TXD: J2.1, U15.37 (TXD0)
USB_DN: U15.13 (USB_D-), U16.6 (I/O1)
USB_DP: U15.14 (USB_D+), U16.4 (I/O2)
